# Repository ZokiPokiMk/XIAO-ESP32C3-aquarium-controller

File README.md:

# XIAO-ESP32C3-aquarium-controller

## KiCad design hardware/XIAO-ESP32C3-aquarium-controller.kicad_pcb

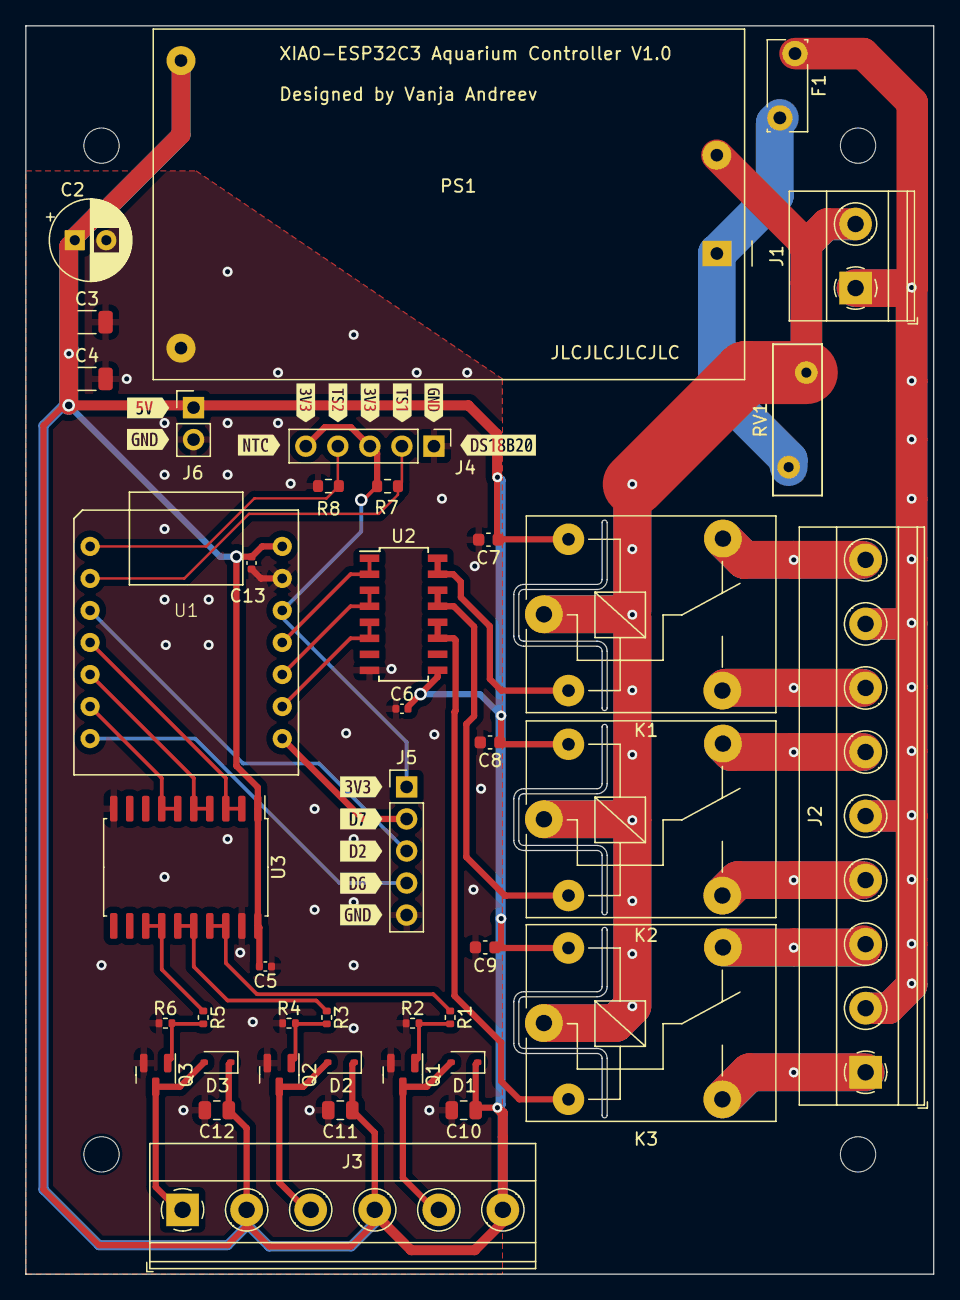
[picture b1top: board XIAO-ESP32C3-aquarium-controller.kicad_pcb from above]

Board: 2 copper layers, 72.0 x 99.0 mm, 59 parts (0 on the bottom side), 35 nets.

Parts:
C2: 220uF; CP_Radial_D6.3mm_P2.50mm
C3, C4: 47uF; C_1206_3216Metric
C5, C6: 1uF; C_0402_1005Metric
C7, C8, C9: 10uF; C_0603_1608Metric
C10, C11, C12: 22uF; C_0805_2012Metric
C13: 4.7uF; C_0402_1005Metric
D1, D2, D3: 1N4148WS; D_SOD-323
F1: 0.5A; Fuse
H1, H2, H3, H4: MountingHole; MountingHole_2.8mm_M2.6
J1: Conn_01x02; TerminalBlock_Phoenix_MKDS-1,5-2-5.08_1x02_P5.08mm_Horizont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
J2: Conn_01x07; TerminalBlock_Phoenix_MKDS-1,5-9-5.08_1x09_P5.08mm_Horizont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
J3: Conn_01x06; TerminalBlock_Phoenix_MKDS-1,5-6-5.08_1x06_P5.08mm_Horizont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
J4, J5: Conn_01x03; PinHeader_1x05_P2.54mm_Vertical
J6: Conn_01x02; PinHeader_1x02_P2.54mm_Vertical
K1, K2, K3: SANYOU_SRD_Form_C; Relay_SPDT_SANYOU_SRD_Series_Form_C
PS1: HLK-PM01; Converter_ACDC_HiLink_HLK-10Mxx
Q1, Q2, Q3: AO3400A; SOT-23
R1, R3, R5: 100; R_0402_1005Metric
R2, R4, R6: 10K; R_0402_1005Metric
R7: 4K7; R_0603_1608Metric
R8: 10K; R_0603_1608Metric
RV1: 10D561; RV_Disc_D12mm_W3.9mm_P7.5mm
U1: XIAO-ESP32C3
U2: ULN2003; SOIC-16W_ULN2003ADR
U3: 74HC245; SOIC-20W_7.5x12.8mm_P1.27mm
kibuzzard-65101B66: G***; kibuzzard-65101B66
kibuzzard-65101BA1: G***; kibuzzard-65101BA1
kibuzzard-65101BBB: G***; kibuzzard-65101BBB
kibuzzard-65101BCD: G***; kibuzzard-65101BCD
kibuzzard-65101BE1: G***; kibuzzard-65101BE1
kibuzzard-65101C3C: G***; kibuzzard-65101C3C
kibuzzard-65101C61: G***; kibuzzard-65101C61
kibuzzard-65101CEA, kibuzzard-65101CEA#2: G***; kibuzzard-65101CEA
kibuzzard-65101D0B: G***; kibuzzard-65101D0B
kibuzzard-65101D31: G***; kibuzzard-65101D31
kibuzzard-65101D45: G***; kibuzzard-65101D45
kibuzzard-65102A38: G***; kibuzzard-65102A38
kibuzzard-65102A64: G***; kibuzzard-65102A64

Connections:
+3.3V: J4.3, J4.5, J5.1, R7.1, U1.12 (3V3)
+5V: C2.1, C3.1, C4.1, C5.2, C6.2, C7.1, C8.1, C9.1, C10.1, C11.1, C12.1, C13.2, D1.1 (K), D2.1 (K), D3.1 (K), J3.2, J3.4, J3.6, J6.1, K1.5, K2.5, K3.5, PS1.4 (+Vout), U1.14 (5V), U2.9 (COM), U3.1 (A->B), U3.20 (VCC)
/D2: J5.3, U1.3 (PA10_A2_D2)
/D6: J5.4, U1.7 (PB08_A6_D6_TX)
/D7: J5.2, U1.8 (PB09_A7_D7_RX)
/MosfetRelay1/Vout: D1.2 (A), J3.5, Q1.3 (D)
/MosfetRelay2/Vout: D2.2 (A), J3.3, Q2.3 (D)
/MosfetRelay3/Vout: D3.2 (A), J3.1, Q3.3 (D)
/RS1: U1.6 (PA9_A5_D5_SCL), U3.6 (A4), U3.7 (A5)
/RS2: U1.5 (PA8_A4_D4_SDA), U3.4 (A2), U3.5 (A3)
/RS3: U1.4 (PA11_A3_D3), U3.2 (A0), U3.3 (A1)
/RS5: U1.9 (PA7_A8_D8_SCK), U2.5 (I5), U2.6 (I6)
/RS6: U1.10 (PA5_A9_D9_MISO), U2.3 (I3), U2.4 (I4)
/RS7: U1.11 (PA6_A10_D10_MOSI), U2.1 (I1), U2.2 (I2)
/Relay1/NC: J2.7, K1.3
/Relay1/NO: J2.9, K1.4
/Relay2/NC: J2.4, K2.3
/Relay2/NO: J2.6, K2.4
/Relay3/NC: J2.1, K3.3
/Relay3/NO: J2.3, K3.4
/TS1: J4.2, R7.2, U1.2 (PA4_A1_D1)
/TS2: J4.4, R8.1, U1.1 (PA02_A0_D0)
/rel1: K1.2, U2.15 (O2), U2.16 (O1)
/rel2: K2.2, U2.13 (O4), U2.14 (O3)
/rel3: K3.2, U2.11 (O6), U2.12 (O5)
/rel5: R1.1, U3.17 (B1), U3.18 (B0)
/rel6: R3.1, U3.15 (B3), U3.16 (B2)
/rel7: R5.1, U3.13 (B5), U3.14 (B4)
AL/L: F1.1, J1.1, J2.2, J2.5, J2.8
AL/N: J1.2, K1.1, K2.1, K3.1, PS1.2 (AC/N), RV1.1
GND: C2.2, C3.2, C4.2, C5.1, C6.1, C7.2, C8.2, C9.2, C10.2, C11.2, C12.2, C13.1, J4.1, J5.5, J6.2, PS1.3 (-Vout), Q1.2 (S), Q2.2 (S), Q3.2 (S), R2.1, R4.1, R6.1, R8.2, U1.13 (GND), U2.8 (GND), U3.10 (GND), U3.19 (CE)
unnamed: F1.2, PS1.1 (AC/L), RV1.2
unnamed: Q1.1 (G), R1.2, R2.2
unnamed: Q2.1 (G), R3.2, R4.2
unnamed: Q3.1 (G), R5.2, R6.2

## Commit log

2023-08-20 initial version
2023-08-20 custom fuse footprint with 3d model
2023-08-20 change footpring add cortyard
2023-08-20 update footprint with CrtYd
2023-08-20 added new connector, increase copper for al/n
2023-08-20 ignore lck files
2023-08-20 Create LICENSE
2023-08-22 'GND input pad' and 'C2 GND pad' pad-connection:solid
2023-08-22 additional route for 5V input on B.Cu
2023-08-25 capacitor at mosfet
2023-08-25 add + pad for 5V
2023-08-25 ticker pads for relay
2023-08-31 fixed 10K resistor for NTC Thermistor
2023-09-01 changes in pcb size and holes for case fitting
2023-09-17 changes in AC tracks
2023-09-20 changes in tracks, spacing....
2023-09-21 some track fixes
2023-09-21 change tantalum capacitor to ceramic
2023-09-21 3v3 instead 5v on connector
2023-09-21 double sided tracks
2023-09-21 capacitor for ESP32C3
2023-09-22 origins change
2023-09-22 change hole size
2023-09-24 labels
2023-09-24 5V/GND connector
2023-09-26 some bom exclusions, jlcpcb rotations
2023-09-26 labeling
2023-09-30 text change
2023-09-30 add aditional 5V track
2023-10-23 move some 5V track because of GND padding
2023-12-01 fix JLCPCB Part #
2023-12-14 fix XIAO-ESP32C3 footprint
2023-12-14 fix after new footprint
